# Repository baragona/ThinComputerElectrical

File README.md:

# ThinComputerElectrical
Thin Computer Electrical design

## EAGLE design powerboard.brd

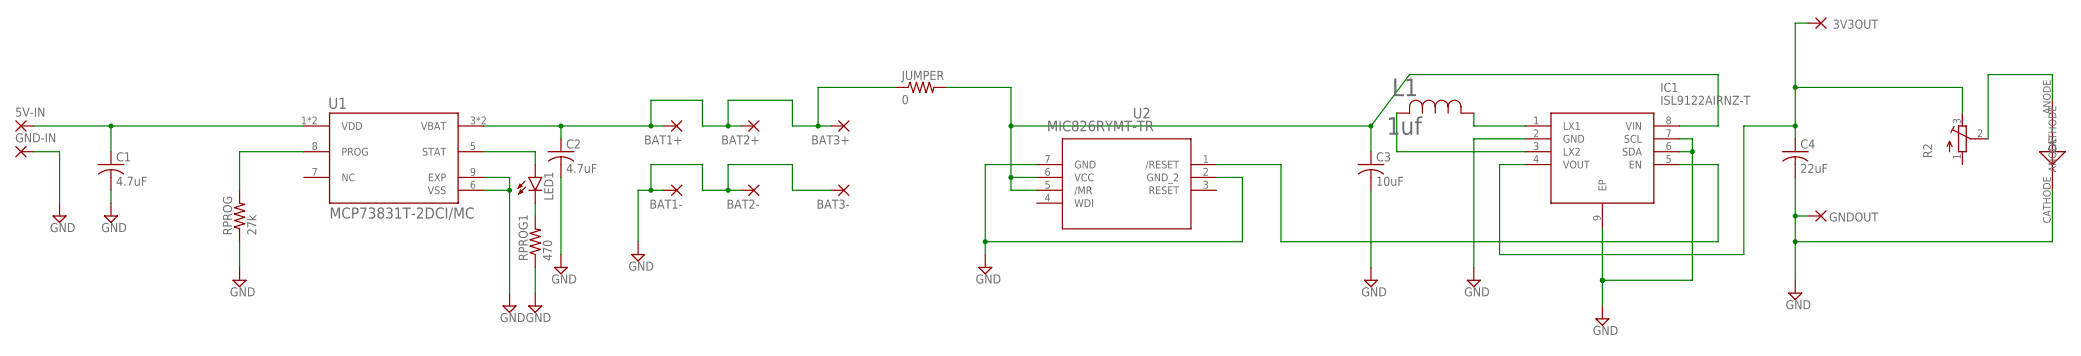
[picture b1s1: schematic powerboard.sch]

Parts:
3V3OUT, 5V-IN: 2,54/0,9
BAT1+, BAT1-, BAT2+, BAT2-, BAT3+, BAT3-: 2,54/0,9
C1, C2: 4.7uF; C0603K
C3: 10uF; C0603K
C4: 22uF; C0603K
GND-IN: 2,54/0,9
GNDOUT: 2,54/0,9
IC1: ISL9122AIRNZ-T; SON50P300X200X100-9N
JUMPER: 0; R0805
L1: 1uf; IND_IHHP-0806ZH-01_VIS
LED1: LEDCHIPLED_0603; CHIPLED_0603
R2: R-TRIMM3165W; RTRIM3165W
RPROG: 27k; R0402
RPROG1: 470; R0402
U1: MCP73831T-2DCI/MC; SON50P200X300X100-9N
U2: MIC826RYMT-TR; UDFN6_HKA_MCH
U$1: CHIPLED; CHIPLED2828

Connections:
3.3REGULATED: 3V3OUT.1, C4.1, IC1.4 (VOUT), R2.3 (E)
5VIN: 5V-IN.1, C1.1, U1.1 (VDD), U1.2 (VDD)
BAT_IN: C3.1, IC1.8 (VIN), JUMPER.2, U2.5 (/MR), U2.6 (VCC)
GND: BAT1-.1, BAT2-.1, BAT3-.1, C1.2, C2.2, C3.2, C4.2, GND-IN.1, GNDOUT.1, IC1.2 (GND), IC1.6 (SDA), IC1.7 (SCL), IC1.9 (EP), RPROG.1, RPROG1.1, U1.6 (VSS), U1.9 (EXP), U2.2 (GND_2), U2.7 (GND), U$1.CATHODE
INDUCTOR1: IC1.3 (LX2), L1.2
INDUCTOR2: IC1.1 (LX1), L1.1
JUMPER: BAT1+.1, BAT2+.1, BAT3+.1, C2.1, JUMPER.1, U1.3 (VBAT), U1.4 (VBAT)
LED+: R2.2 (S), U$1.ANODE
unnamed: RPROG.2, U1.8 (PROG)
unnamed: LED1.A, U1.5 (STAT)
unnamed: LED1.C, RPROG1.2
unnamed: IC1.5 (EN), U2.1 (/RESET)

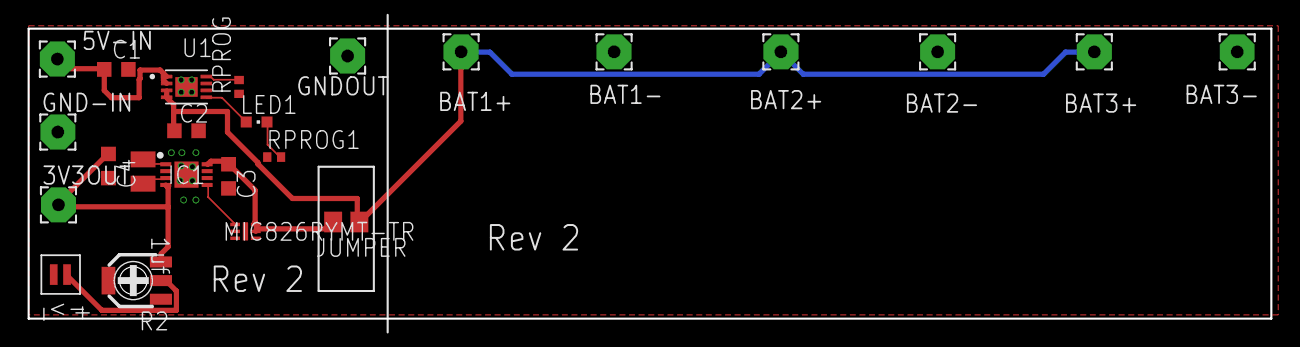
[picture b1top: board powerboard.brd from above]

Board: 2 copper layers, 90.0 x 21.0 mm, 24 parts (0 on the bottom side), 12 nets.

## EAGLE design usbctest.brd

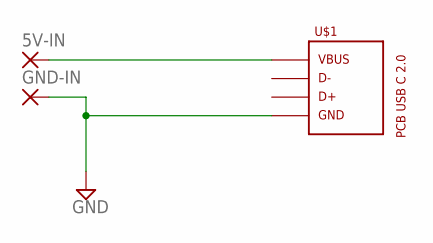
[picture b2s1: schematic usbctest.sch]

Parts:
5V-IN: 2,54/0,9
GND-IN: 2,54/0,9
U$1: PCB_USB_C_2.0W_2; USB_TYPE_C_W_2.0_2

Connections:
5VIN: 5V-IN.1, U$1.VBUS
GND: GND-IN.1, U$1.GND

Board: 2 copper layers, 3 parts (0 on the bottom side), 2 nets, no tracks yet.

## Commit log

2023-01-25 init
2023-01-26 place some parts
2023-01-27 progress
2023-01-27 add jlc rules, edit mic826 footprint
2023-01-27 finish
2023-01-28 add gerber export
2023-01-28 add notes
2023-02-06 add schematic pdf
2023-02-06 add digikey bom
2023-02-19 update powerboard with fixes

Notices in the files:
parts and their libraries:
COPYRIGHT: Copyright (C) 2023 Ultra Librarian. All rights reserved.
